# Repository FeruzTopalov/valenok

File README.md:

## **VALENOK** - yet another DS18B20 thermometer, but...

<p align="center">
  
  <br>
  <a href="https://youtu.be/WqwGhjjpDnw">https://youtu.be/WqwGhjjpDnw</a>
</p>

* Eyes-friendly static indication
* Zero-consumption when IDLE, years without battery replacement
* Single button interface
* Only temperature - who the f**k needs more?
* Totally open-source/open-hardware
* Easy solderable - 0805 chip components and huuuge SMD packages

## Hardware

Well, it is a typical KiCad project, schematic + PCB. Also there are prepared gerbers, so if you don't want to deal with KiCad, just zip "gerbers" folder and send it to your PCB supplier. 

Schematic is pretty simple. Q1 and Q2 are power switch, which is controlled via MCU. Q3 is a "HC595 anti-glitch" which controls the sift registers state at power-up. By the way, switch SW1 powers on the thermometer, after that MCU holds Q2's gate until the end of the program.

As you can see, power switch and shift registers are controlled using common pin PB4 (POW_MR_OE_CTRL). That trick is here in order to clear the shift registers (HC595) at startup. The algorithm is following:

* User pushes the SW1
* PB4 is low, power is not engaged by Q2
* OE is high due to inversion at the Q3, outputs of the shift registers are in Hi-Z
* MR is low, shift registers are cleared
* Firmware strikes a strobe to the shift registers ST inputs, the content of the shift registers (which are empty) are copied to the outputs
* Finally, MCU rise up PB4, engage the power switch and enables the shift registers outputs
* You see empty 7-seg display, no randomly blinking segments anymore... PROFIT!

_See 'Pictures/Trick.jpg' for details_

## Firmware

Written in assembler using pretty old AVR Studio 4.19, therefore i publish only the listing but not the project file. I you want to compile by yourself, use any appropriate AVR compiler or find AVR Studio 4.19 on the internet. Anyway there is a ready .hex file to flash.

Firmware flow:
* Clear HC595 registers
* Hold the power
* Blink all segments for 100 ms in order to check their functionality
* Check sensor presence, show "---" if not connected
* Read the temperature
* Calculate CRC, show "crc" if mismatch
* Check DS18B20 for 12-bit mode, if not then switch to 12-bit mode
* Perform temperature rounding +-0.5 Celsius degree
* Prepare display content and show
* Hold on for 3 sec
* Release the power

Flashing is also simple, the only thing you should aware is that you have to change fuse bits. Tiny13A's factory default fuses are LOW:0x6A; HIGH:0xFF. To make thermometer works it is only needed to switch off internal clock division by 8 (CKDIV8). Therefore only LOW fuse is affected, it's value changes from LOW:0x6A to LOW:0x7A - that simple. I recommend to use AVRDUDESS (https://github.com/zkemble/AVRDUDESS). 

## Enclosure

It is designed to be placed in a market available GAINTA G1068G/G1068B enclosure. It has dimensions of 95 x 48 x 38 mm. 

PCB is fixed to the smaller lid using 20 mm Male-Female Hex standoffs; 3x AA batteries with no holder are placed underneath the PCB.

In "dxf" folder you can find a guide where to make holes - one for 7-Seg display, one for button:

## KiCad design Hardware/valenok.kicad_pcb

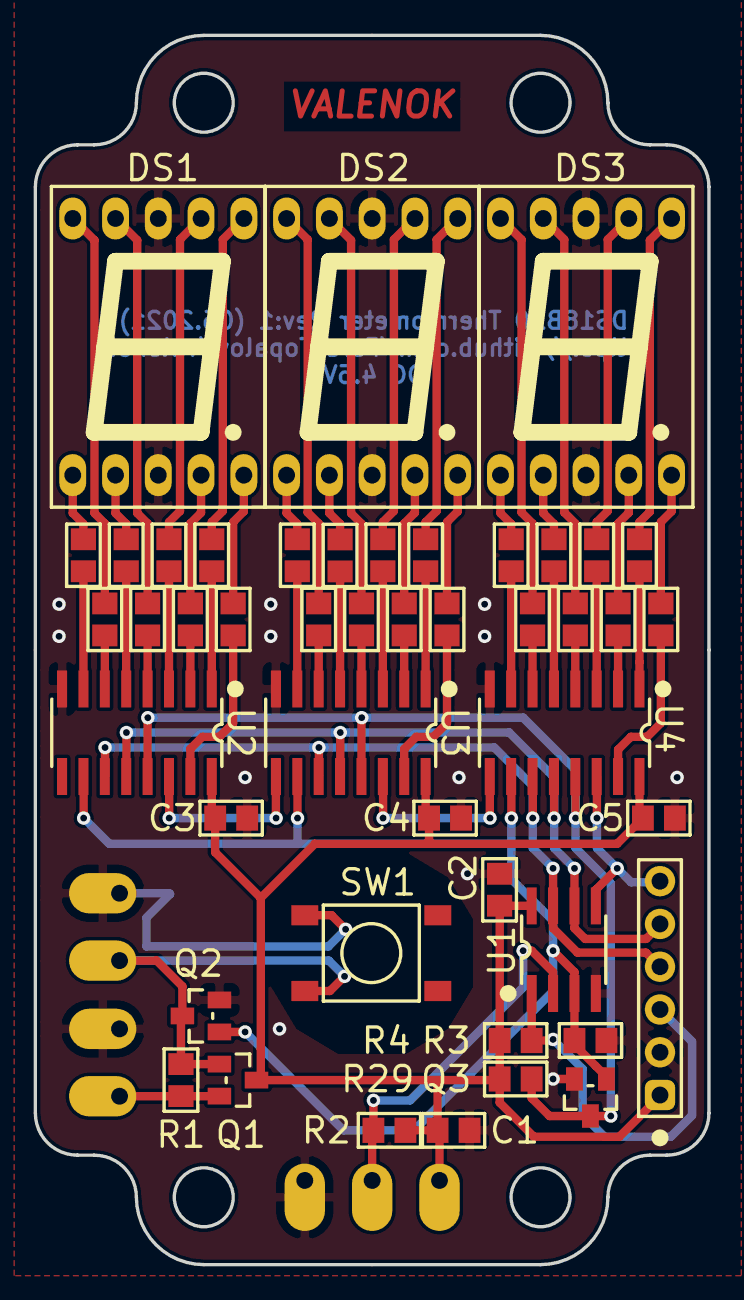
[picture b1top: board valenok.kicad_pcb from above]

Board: 2 copper layers, 40.0 x 73.0 mm, 53 parts (0 on the bottom side), 61 nets.

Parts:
C1, C2, C3, C4, C5: 100n; C0805
DS1, DS2, DS3: SC56-11GWA; 7seg_0.56in
Q1: AO3407A; SOT-23
Q2, Q3: AO3400; SOT-23
R1, R3, R4, R29: 56k; R0805
R2: 4.7k; R0805
R5, R6, R7, R8, R9, R10, R11, R12, R13, R14, R15, R16, R17, R18, R19, R20, R21, R22, R23, R24, R25, R26, R27, R28: 470; R0805
SW1: KLS7-TS6604-4.3; 6x6switch
U1: ATtiny13A; SOIC-8
U2, U3, U4: 74HC595; SOIC-16
X1: Bat+; Pad
X2: Bat-; Pad
X3, X4: SW; Pad
X5: DSVCC; Pad
X6: DSDQ; Pad
X7: DSGND; Pad
X8: PLS-1x6; 1x6header

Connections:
/1A: R5.2, U2.3
/1B: R6.2, U2.1
/1C: R7.2, U2.2
/1D: R8.2, U2.5
/1E: R9.2, U2.7
/1F: R10.2, U2.4
/1G: R11.2, U2.6
/1P: R12.2, U2.15
/2A: R13.2, U3.3
/2B: R14.2, U3.1
/2C: R15.2, U3.2
/2D: R16.2, U3.5
/2E: R17.2, U3.7
/2F: R18.2, U3.4
/2G: R19.2, U3.6
/2P: R20.2, U3.15
/3A: R21.2, U4.3
/3B: R22.2, U4.1
/3C: R23.2, U4.2
/3D: R24.2, U4.5
/3E: R25.2, U4.7
/3F: R26.2, U4.4
/3G: R27.2, U4.6
/3P: R28.2, U4.15
DS18B20_DQ: R2.2, U1.2, X6.1
GND: C1.2, C2.2, C3.2, C4.2, C5.2, DS1.3, DS1.8, DS2.3, DS2.8, DS3.3, DS3.8, Q2.2, Q3.2, R3.2, SW1.1, U1.4, U2.8, U3.8, U4.8, X2.1, X4.1, X7.1, X8.2
HC595_DS: U1.5, U4.14, X8.6
HC595_OE: Q3.3, R29.2, U2.13, U3.13, U4.13
HC595_SH: U1.7, U2.11, U3.11, U4.11, X8.4
HC595_ST: U1.6, U2.12, U3.12, U4.12, X8.5
MCU_RESET: R4.2, U1.1, X8.3
unnamed: DS1.1, R9.1
unnamed: DS1.2, R8.1
unnamed: DS1.4, R7.1
unnamed: DS1.5, R12.1
unnamed: DS1.6, R6.1
unnamed: DS1.7, R5.1
unnamed: DS1.9, R10.1
unnamed: DS1.10, R11.1
unnamed: DS2.1, R17.1
unnamed: DS2.2, R16.1
unnamed: DS2.4, R15.1
unnamed: DS2.5, R20.1
unnamed: DS2.6, R14.1
unnamed: DS2.7, R13.1
unnamed: DS2.9, R18.1
unnamed: DS2.10, R19.1
unnamed: DS3.1, R25.1
unnamed: DS3.2, R24.1
unnamed: DS3.4, R23.1
unnamed: DS3.5, R28.1
unnamed: DS3.6, R22.1
unnamed: DS3.7, R21.1
unnamed: DS3.9, R26.1
unnamed: DS3.10, R27.1
unnamed: Q1.2, R1.1, X1.1
unnamed: U2.14, U3.9
unnamed: U3.14, U4.9
POW_MR_OE_CTRL: Q2.1, Q3.1, R3.1, U1.3, U2.10, U3.10, U4.10
POW_SW: Q1.1, Q2.3, R1.2, SW1.3, X3.1
VCC: C1.1, C2.1, C3.1, C4.1, C5.1, Q1.3, R2.1, R4.1, R29.1, U1.8, U2.16, U3.16, U4.16, X5.1, X8.1

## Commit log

2021-06-05 First release
2021-06-05 Fix images extensions
2021-06-05 Edit README
